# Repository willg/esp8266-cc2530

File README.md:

# ESP8266 + CC2530
Board to integrate an ESP8266 + CC2530 + RF Front end

# RF Parts
[CC2530F256(radio)](https://lcsc.com/product-detail/RF-Transceiver-ICs_Texas-Instruments_CC2530F256RHAR_Texas-Instruments-TI-CC2530F256RHAR_C9120.html/?href=jlc-SMT)

## RF Front Ends
### RFX2401C
[RFX2401C](https://lcsc.com/product-detail/RF-Transceiver-ICs_Skyworks-Solutions_RFX2401C_Skyworks-Solutions-RFX2401C_C19213.html/?href=jlc-SMT)

> This is the RF front end that was on the 2530PA module I got from
> [Bangood](https://www.banggood.com/CC2530-UART-Wireless-Core-Development-Board-CC2530F256-Serial-Port-Wireless-Module-2_4GHz-For-Zigbee-p-1445025.html?utm_design=41&utm_source=emarsys&utm_medium=Neworder171109&utm_campaign=trigger-emarsys&utm_content=winna&sc_src=email_2675773&sc_eh=ddc2dc193b00c4611&sc_llid=10757429&sc_lid=105229698&sc_uid=wcY1TUr67W&cur_warehouse=CN),

RFX2401C Mode Truth Table:
| TXEN | RXEN | Mode |
| --- | --- | --- |
| 1 | X | TX Active
| 0 | 1 | RX Active
| 0 | 0 | Chip shutdown

CC2530 Control Connections **UNTESTED**:
| CC2530 | RFX2401C |
| --- | --- |
| P1_0 | RXEN
| P1_1 | TXEN

### CC2592
[CC2592](https://lcsc.com/product-detail/RF-Transceiver-ICs_Texas-Instruments_CC2592RGVR_Texas-Instruments-TI-CC2592RGVR_C53274.html/?href=jlc-SMT)

CC2592 Mode Truth Table:
| PA_EN | LNA_EN | HGM | Mode |
| --- | --- | --- | --- |
| 0 | 0 | X | Power Down
| X | 1 | 0 | RX Low-gain
| X | 1 | 1 | RX High-gain
| 1 | 0 | X | TX

CC2530 Control Connections:
| CC2592 | CC2530 |
| --- | --- |
| EN (LNA_EN) | P1_0
| PA_EN | P1_1
| HGM | P0_7
[Source](https://processors.wiki.ti.com/index.php/Enabling_the_Support_of_CC259x_PA/LNA_with_Z-Stack-Home)

### CC2591
This part is not recommended for new designs, and is out of stock at LCSC

## Regulator
[AMS1117-3.3](https://lcsc.com/product-detail/Low-Dropout-Regulators-LDO_AMS_AMS1117-3-3_AMS1117-3-3_C6186.html/?href=jlc-SMT)

AMS1117-3.3 Bypass. >22uF Tantalum 
[100uF 6.3V](https://lcsc.com/product-detail/Tantalum-Capacitors_AVX_TAJB107K006RNJ_100uF-107-10-6-3V_C16133.html/?href=jlc-SMT)

# ESP8266
## Option 1
Use Wemos D1-mini and interface via header

## Option 2
Use ESP8266MOD and integrate onto board
[ESP8266MOD](https://lcsc.com/product-detail/WIFI-Modules_ESP-12F-ESP8266MOD_C82891.html)
> not available for JLPCB to assemble

[CH340C (USB-UART
bridge)](https://lcsc.com/product-detail/USB_CH340C_C84681.html/?href=jlc-SMT)

# CC2530PA Notes
CC2530PA from banggood's connections:
| RFX2401C | CC2530 |
| --- | --- |
| TXEN | P1_5
| RXEN | P1_4

> I modified the z-stack zigbee firmware to have TXEN on PA1_5 and RXEN on P1_4
> and improved RF performance over the stock CC2530_CC2592 firmware, and seemed
> to be better than the CC2531 USB stick I have

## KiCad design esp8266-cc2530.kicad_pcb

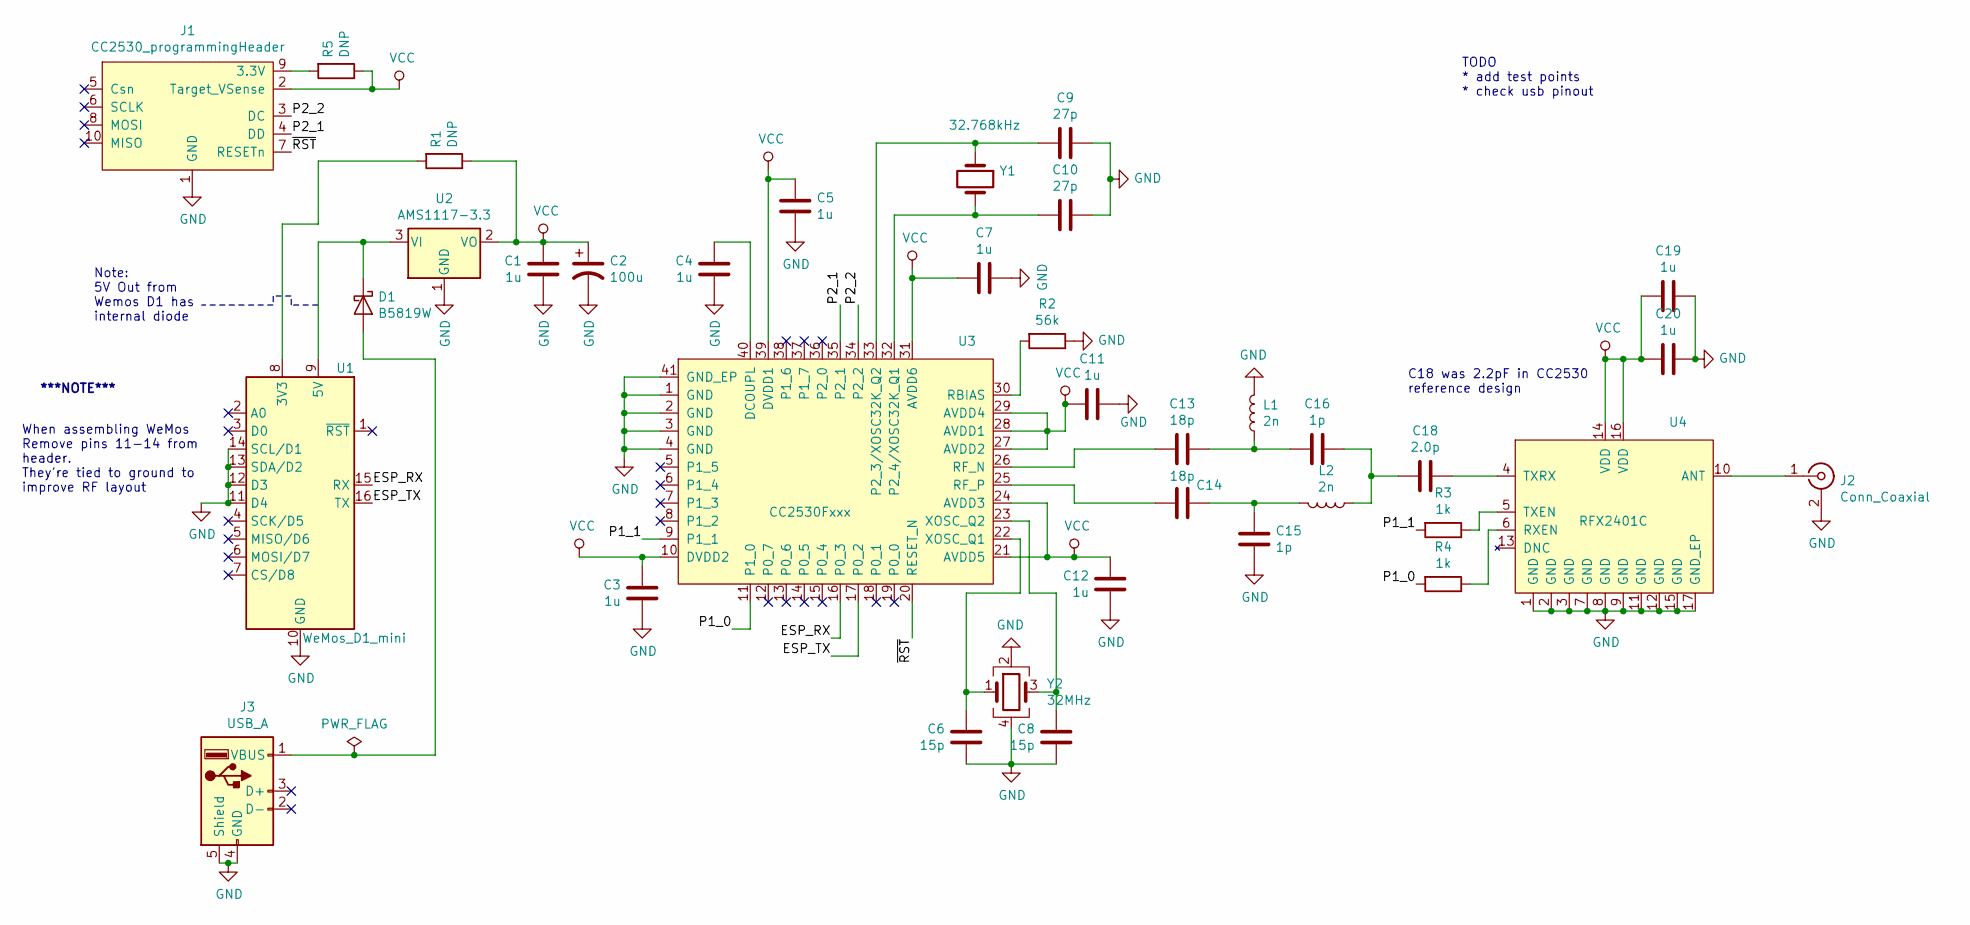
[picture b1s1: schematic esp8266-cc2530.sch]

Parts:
C1, C3, C4, C5, C7, C11, C12, C19, C20: 1u; C_0805_2012Metric; LCSC C28323
C2: 100u; CP_EIA-3528-21_Kemet-B; LCSC C16133
C6, C8: 15p; C_0805_2012Metric; JLCPCB Basic Y
C9, C10: 27p; C_0805_2012Metric; JLCPCB Basic Y
C13, C14: 18p; C_0805_2012Metric; JLCPCB Basic Y
C15, C16: 1p; C_0805_2012Metric; JLCPCB Basic Y
C18: 2.0p; C_0805_2012Metric; LCSC C1800
D1: B5819W; D_SOD-123; LCSC C8598
J1: CC2530_programmingHeader; PinHeader_2x05_P1.27mm_Vertical_SMD; LCSC C124391
J2: Conn_Coaxial; CON-SMA-EDGE-S(RP)
J3: USB_A; Molex_48037-2200_USB-A
L1, L2: 2n; L_0603_1608Metric; JLCPCB Basic No JLCPCB Assembly
R1, R5: DNP; R_0805_2012Metric
R2: 56k; R_0805_2012Metric; JLCPCB Basic Y
R3, R4: 1k; R_0805_2012Metric; JLCPCB Basic Y
U1: WeMos_D1_mini; WEMOS_D1_mini_smt
U2: AMS1117-3.3; SOT-223-3_TabPin2; LCSC C6186
U3: CC2530Fxxx; QFN-40-1EP_6x6mm_P0.5mm_EP4.6x4.6mm; LCSC C9120
U4: RFX2401C; QFN-16-1EP_3x3mm_P0.5mm_EP1.7x1.7mm; LCSC C19213
Y1: 32.768kHz; Crystal_SMD_3215-2Pin_3.2x1.5mm; LCSC C32346
Y2: 32MHz; Crystal_SMD_SeikoEpson_FA238-4Pin_3.2x2.5mm; LCSC C91742

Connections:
/ESP_RX: U1.15 (RX), U3.16 (P0_3)
/ESP_TX: U1.16 (TX), U3.17 (P0_2)
/P1_0: R4.2, U3.11 (P1_0)
/P1_1: R3.2, U3.9 (P1_1)
/P2_1: J1.4 (DD), U3.35 (P2_1)
/P2_2: J1.3 (DC), U3.34 (P2_2)
/~RST: J1.7 (RESETn), U3.20 (RESET_N)
GND: C1.1, C2.2, C3.1, C4.1, C5.2, C6.1, C7.2, C8.1, C9.1, C10.1, C11.2, C12.1, C15.2, C19.2, C20.2, J1.1 (GND), J2.2 (Ext), J3.4 (GND), J3.5 (Shield), L1.2, R2.1, U1.10 (GND), U1.11 (D4), U1.12 (D3), U1.13 (SDA/D2), U1.14 (SCL/D1), U2.1 (GND), U3.1 (GND), U3.2 (GND), U3.3 (GND), U3.4 (GND), U3.41 (GND_EP), U4.1 (GND), U4.2 (GND), U4.3 (GND), U4.7 (GND), U4.8 (GND), U4.9 (GND), U4.11 (GND), U4.12 (GND), U4.15 (GND), U4.17 (GND_EP), Y2.2, Y2.4
unnamed: C4.2, U3.40 (DCOUPL)
unnamed: C6.2, U3.22 (XOSC_Q1), Y2.1
unnamed: C8.2, U3.23 (XOSC_Q2), Y2.3
unnamed: C9.2, U3.33 (P2_3/XOSC32K_Q2), Y1.1
unnamed: C10.2, U3.32 (P2_4/XOSC32K_Q1), Y1.2
unnamed: C13.1, U3.26 (RF_N)
unnamed: C13.2, C16.1, L1.1
unnamed: C14.1, U3.25 (RF_P)
unnamed: C14.2, C15.1, L2.2
unnamed: C16.2, C18.1, L2.1
unnamed: C18.2, U4.4 (TXRX)
unnamed: D1.1 (K), U1.9 (5V), U2.3 (VI)
unnamed: D1.2 (A), J3.1 (VBUS)
unnamed: J1.9 (3.3V), R5.2
unnamed: J2.1 (In), U4.10 (ANT)
unnamed: R1.2, U1.8 (3V3)
unnamed: R2.2, U3.30 (RBIAS)
unnamed: R3.1, U4.5 (TXEN)
unnamed: R4.1, U4.6 (RXEN)
VCC: C1.2, C2.1, C3.2, C5.1, C7.1, C11.1, C12.2, C19.1, C20.1, J1.2 (Target_VSense), R1.1, R5.1, U2.2 (VO), U3.10 (DVDD2), U3.21 (AVDD5), U3.24 (AVDD3), U3.27 (AVDD2), U3.28 (AVDD1), U3.29 (AVDD4), U3.31 (AVDD6), U3.39 (DVDD1), U4.14 (VDD), U4.16 (VDD)

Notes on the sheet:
TODO * add test points * check usb pinout
C18 was 2.2pF in CC2530 reference design
***NOTE***
When assembling WeMos Remove pins 11-14 from header. They're tied to ground to improve RF layout
Note: 5V Out from Wemos D1 has internal diode

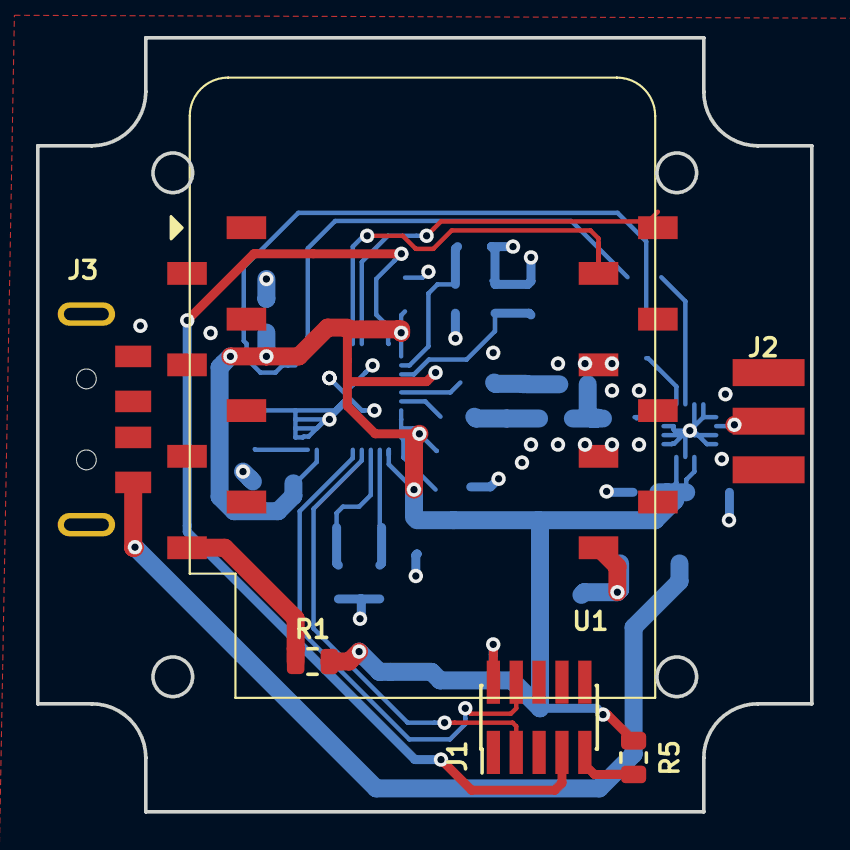
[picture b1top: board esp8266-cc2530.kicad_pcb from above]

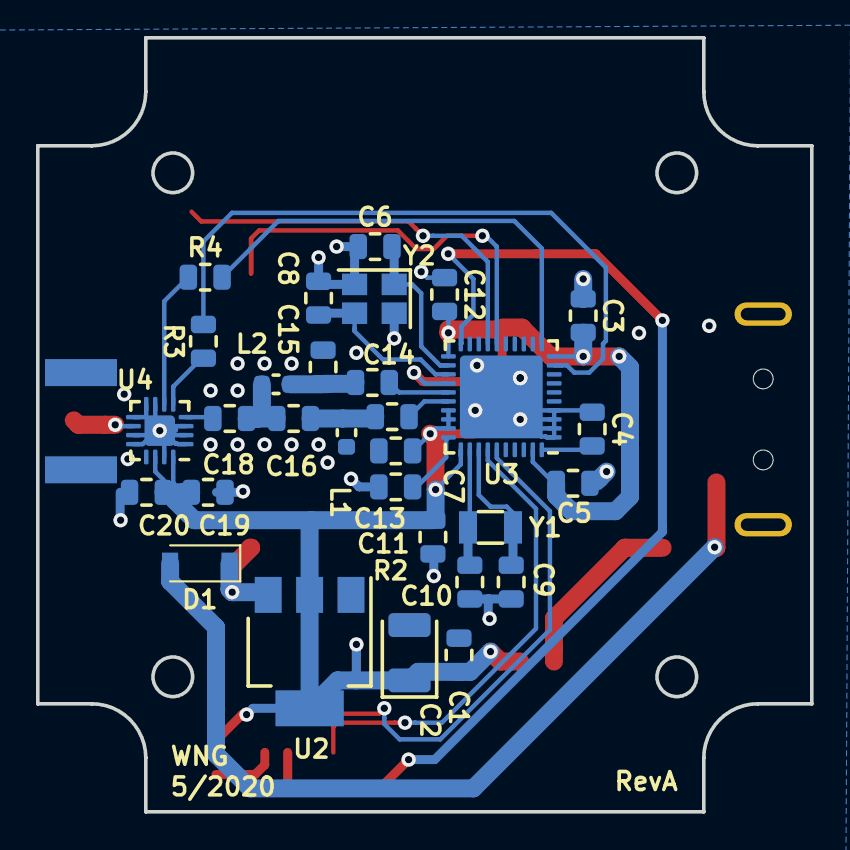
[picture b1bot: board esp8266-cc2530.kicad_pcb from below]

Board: 2 copper layers, 43.0 x 43.0 mm, 36 parts (30 on the bottom side), 28 nets.

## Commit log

2020-04-24 add readme from joplin notes
2020-04-24 readme updates
2020-04-24 cleaning up readme
2020-04-24 created cc2592 part, added to schematic undecided if RF frontend should be RFX2401 or CC2592
2020-04-24 Add table with required CC2530/RFX2401C connections
2020-04-24 Clarify CC2592 table
2020-04-26 added note to readme about testing CC2530PA
2020-04-26 schematic updates * updated TODO * added bypass to RF2401
2020-04-26 add cc2530 programming header
2020-04-27 added regulator for cc2530
2020-04-27 remove cc2592 from schematic
2020-04-27 annotated schematic, fixed DRCs, needed to fork D1-mini symbol
2020-04-27 add formatting line
2020-04-27 begining to assign LCSC part numbers
2020-04-27 footprints assigned to all parts
2020-04-28 added sma connector
2020-04-28 starting to place components. added dxf for potential case
2020-04-28 removed RFX2401 bypass, added DNP to power CC2530 from debugger
2020-04-28 progress on layout
2020-04-30 board laid out
2020-05-01 fixed SMA connector footprint and added 3d model.
    thinking of changing cases... extra board outlines on edge.cuts
2020-05-02 updated layout * new WEMOS D1 footprint and 3d model * switched to case TW5-2-5
2020-05-02 remove unused library from path
2020-05-02 added usb connector, not routed yet
2020-05-03 usb connector routed out
2020-05-04 updated design rules
2020-05-04 remove *.csv from .gitignore to track fabrication files
2020-05-04 add fabrication output
2020-05-08 add GND_EP pin to CC2592
2020-05-08 verified usb connector pinout
